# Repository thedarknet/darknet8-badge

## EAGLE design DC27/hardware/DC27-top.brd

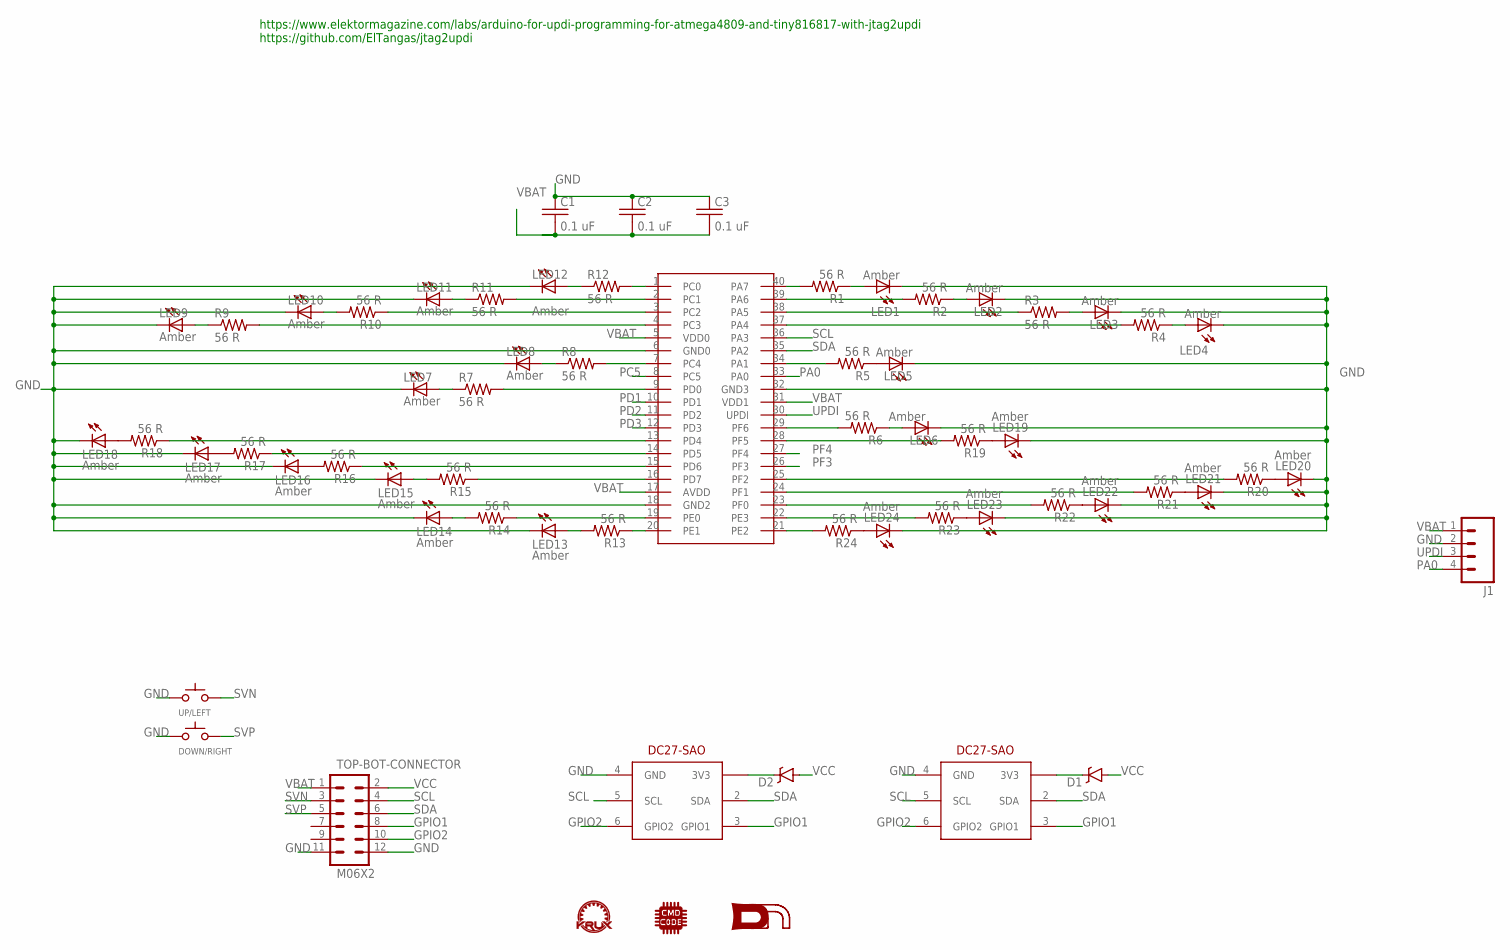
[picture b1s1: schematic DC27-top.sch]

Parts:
C1, C2, C3: 0.1 uF; C1206
D1, D2: DIODE-SCHOTTKYDIOAD-TH; DIOAD1060W80L520D270
DOWN/RIGHT: SWITCH_TACTILETACTILE-2PIN-NARROW; TACTILE-2PIN-NARROW
J1: M04PTH; 1X04
LED1, LED2, LED3, LED4, LED5, LED6, LED7, LED8, LED9, LED10, LED11, LED12, LED13, LED14, LED15, LED16, LED17, LED18, LED19, LED20, LED21, LED22, LED23, LED24: Amber; GULLWING_LED
R1, R2, R3, R4, R5, R6, R7, R8, R9, R10, R11, R12, R13, R14, R15, R16, R17, R18, R19, R20, R21, R22, R23, R24: 56 R; 1206
TOP-BOT-CONNECTOR: M06X2; 2X6
U$1: KRUX_LOGO
U$2: CMD_C0DE_LOGO
U$3, U$4: DC-27-SAO; 3X2
U$5: DN_LOGODC26; DN_LOGO_DC26
U$6: ATMEGA4809-PFATMEL4809-PF; DIP1587W58P254L5175H635Q40B
UP/LEFT: SWITCH_TACTILETACTILE-2PIN-NARROW; TACTILE-2PIN-NARROW

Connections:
GND: C1.1, C2.1, C3.1, DOWN/RIGHT.P$2 (C), J1.2, LED1.C, LED2.C, LED3.C, LED4.C, LED5.C, LED6.C, LED7.C, LED8.C, LED9.C, LED10.C, LED11.C, LED12.C, LED13.C, LED14.C, LED15.C, LED16.C, LED17.C, LED18.C, LED19.C, LED20.C, LED21.C, LED22.C, LED23.C, LED24.C, TOP-BOT-CONNECTOR.11, TOP-BOT-CONNECTOR.12, U$3.4 (GND), U$4.4 (GND), U$6.6 (GND0), U$6.18 (GND2), U$6.32 (GND3), UP/LEFT.P$2 (C)
GPIO1: TOP-BOT-CONNECTOR.8, U$3.3 (GPIO1), U$4.3 (GPIO1)
GPIO2: TOP-BOT-CONNECTOR.10, U$3.6 (GPIO2), U$4.6 (GPIO2)
unnamed: R9.2, U$6.4 (PC3)
unnamed: LED9.A, R9.1
unnamed: R8.2, U$6.7 (PC4)
unnamed: R7.2, U$6.9 (PD0)
unnamed: R1.2, U$6.40 (PA7)
unnamed: R2.2, U$6.39 (PA6)
unnamed: R3.1, U$6.38 (PA5)
unnamed: LED8.A, R8.1
unnamed: LED7.A, R7.1
unnamed: R10.1, U$6.3 (PC2)
unnamed: R11.2, U$6.2 (PC1)
unnamed: R12.2, U$6.1 (PC0)
unnamed: R4.2, U$6.37 (PA4)
unnamed: LED5.A, R5.1
unnamed: R5.2, U$6.34 (PA1)
unnamed: R13.1, U$6.20 (PE1)
unnamed: LED13.A, R13.2
unnamed: R14.1, U$6.19 (PE0)
unnamed: LED14.A, R14.2
unnamed: R15.1, U$6.16 (PD7)
unnamed: LED15.A, R15.2
unnamed: LED17.A, R17.2
unnamed: LED16.A, R16.2
unnamed: R18.1, U$6.13 (PD4)
unnamed: D2.C, U$3.1 (3V3)
unnamed: D1.C, U$4.1 (3V3)
unnamed: R6.2, U$6.29 (PF6)
unnamed: LED6.A, R6.1
unnamed: LED4.A, R4.1
unnamed: LED18.A, R18.2
unnamed: LED1.A, R1.1
unnamed: LED2.A, R2.1
unnamed: R17.1, U$6.14 (PD5)
unnamed: R16.1, U$6.15 (PD6)
unnamed: LED24.A, R24.1
unnamed: LED10.A, R10.2
unnamed: LED11.A, R11.1
unnamed: LED12.A, R12.1
unnamed: LED23.A, R23.1
unnamed: LED22.A, R22.1
unnamed: LED19.A, R19.1
unnamed: LED21.A, R21.1
unnamed: LED20.A, R20.1
unnamed: R19.2, U$6.28 (PF5)
unnamed: R20.2, U$6.25 (PF2)
unnamed: R21.2, U$6.24 (PF1)
unnamed: R22.2, U$6.23 (PF0)
unnamed: R23.2, U$6.22 (PE3)
unnamed: R24.2, U$6.21 (PE2)
unnamed: LED3.A, R3.2
PA0: J1.4, U$6.33 (PA0)
PC5: U$6.8 (PC5)
PD1: U$6.10 (PD1)
PD2: U$6.11 (PD2)
PD3: U$6.12 (PD3)
PF3: U$6.26 (PF3)
PF4: U$6.27 (PF4)
SCL: TOP-BOT-CONNECTOR.4, U$3.5 (SCL), U$4.5 (SCL), U$6.36 (PA3)
SDA: TOP-BOT-CONNECTOR.6, U$3.2 (SDA), U$4.2 (SDA), U$6.35 (PA2)
SVN: TOP-BOT-CONNECTOR.3, UP/LEFT.P$1 (A)
SVP: DOWN/RIGHT.P$1 (A), TOP-BOT-CONNECTOR.5
UPDI: J1.3, U$6.30 (UPDI)
VBAT: C1.2, C2.2, C3.2, J1.1, TOP-BOT-CONNECTOR.1, U$6.5 (VDD0), U$6.17 (AVDD), U$6.31 (VDD1)
VCC: D1.A, D2.A, TOP-BOT-CONNECTOR.2

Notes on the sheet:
https://www.elektormagazine.com/labs/arduino-for-updi-programming-for-atmega4809-and-tiny816817-with-jtag2updi https://github.com/ElTangas/jtag2updi

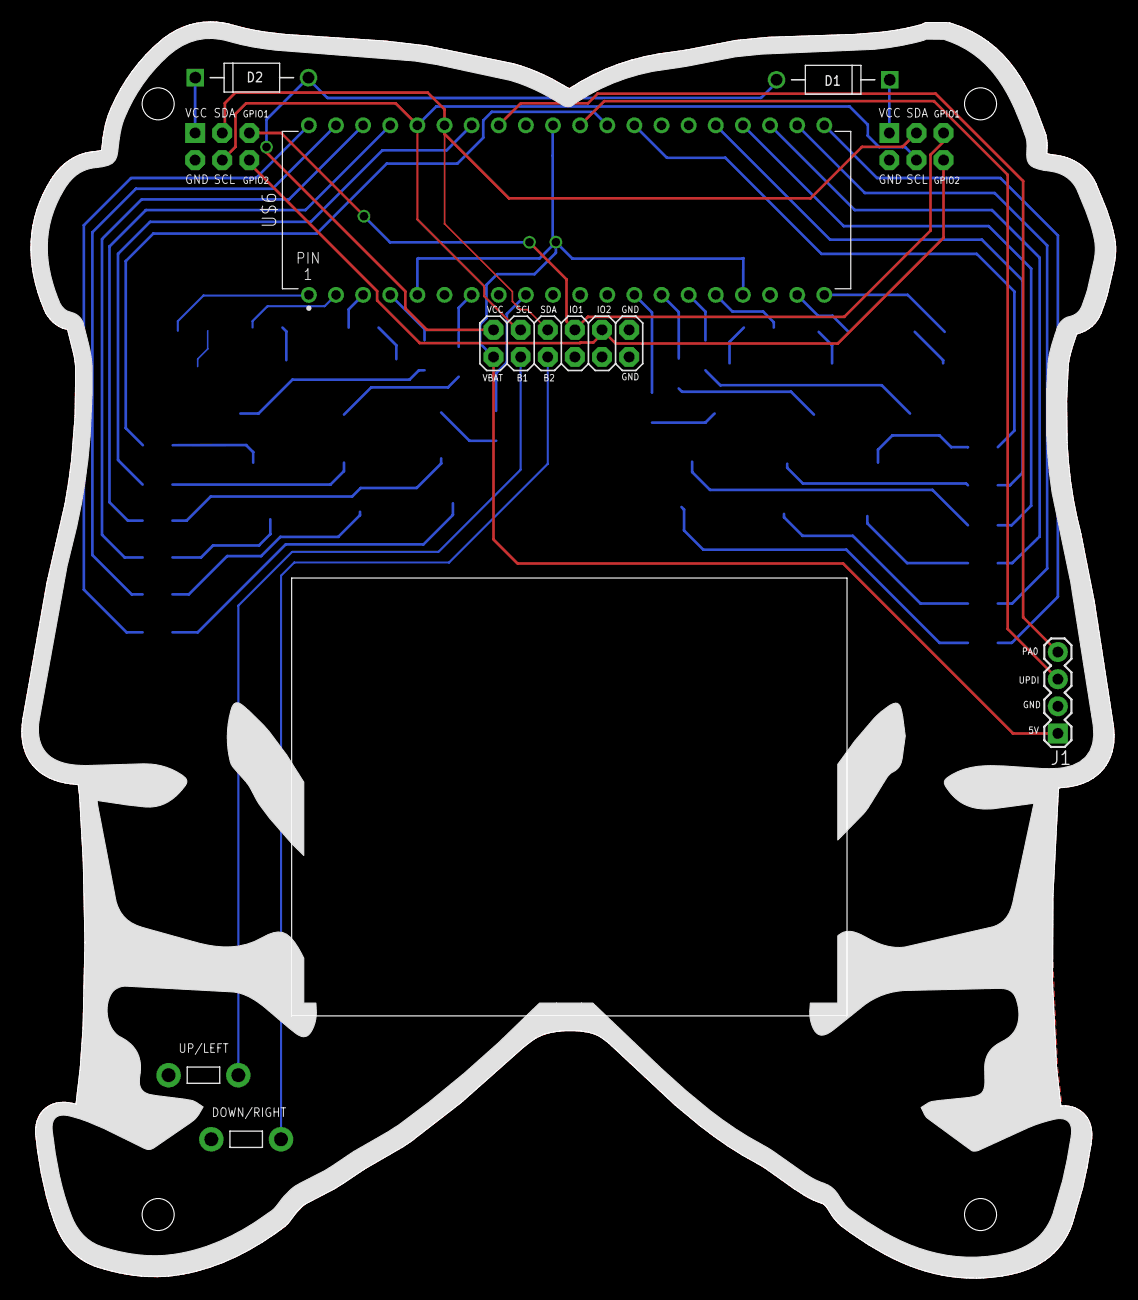
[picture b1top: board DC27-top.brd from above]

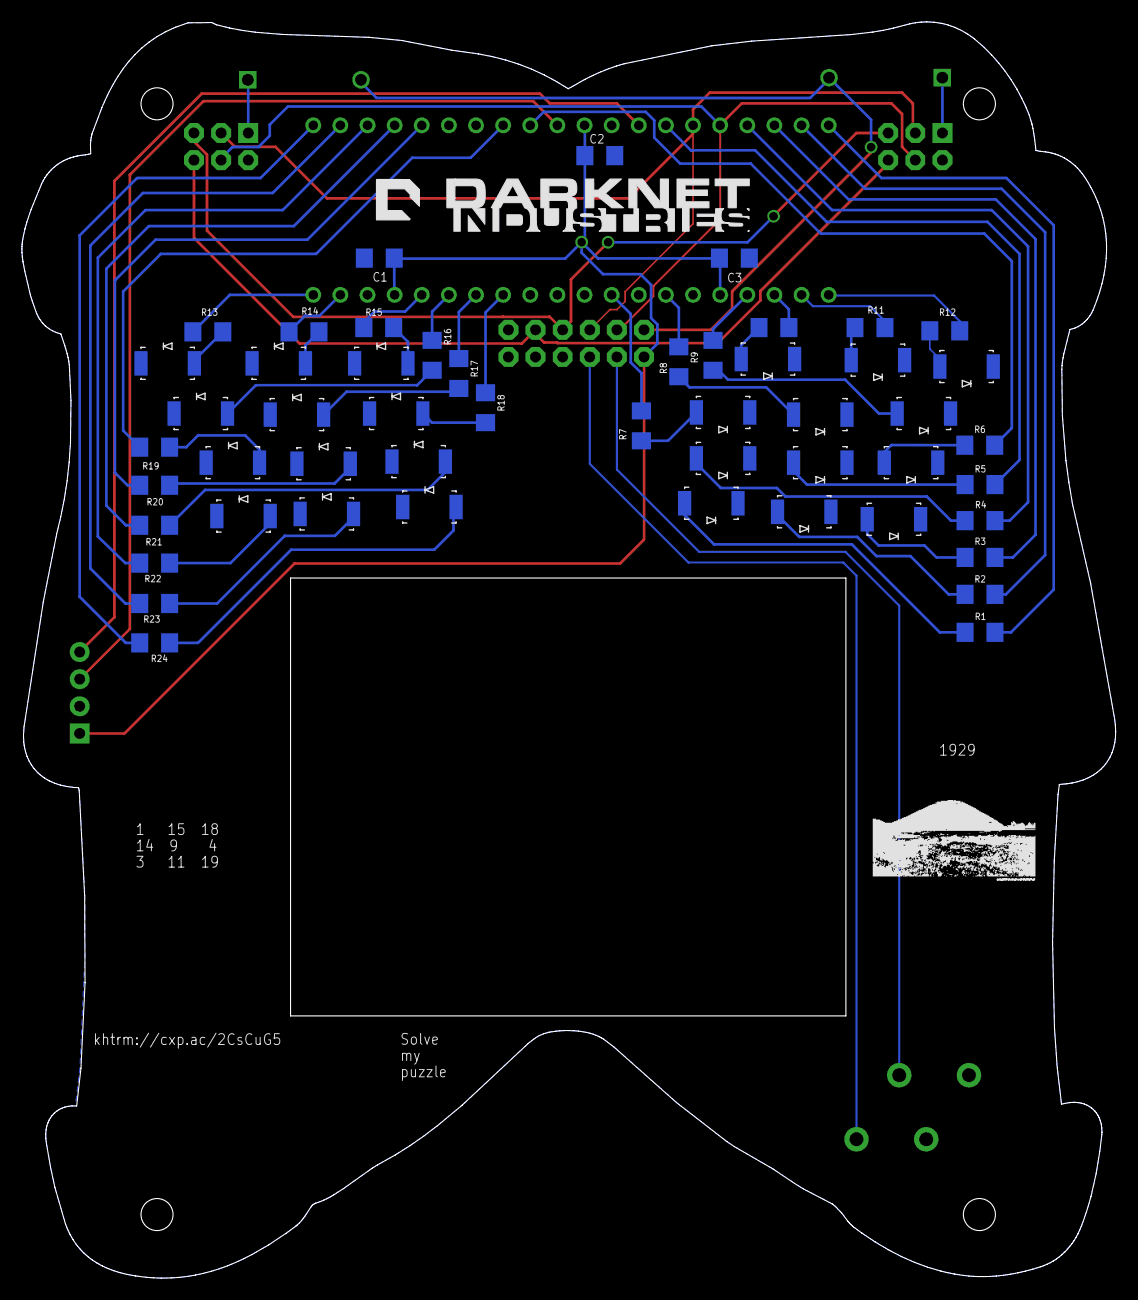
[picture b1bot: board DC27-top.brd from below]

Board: 2 copper layers, 102.4 x 117.6 mm, 63 parts (54 on the bottom side), 61 nets.

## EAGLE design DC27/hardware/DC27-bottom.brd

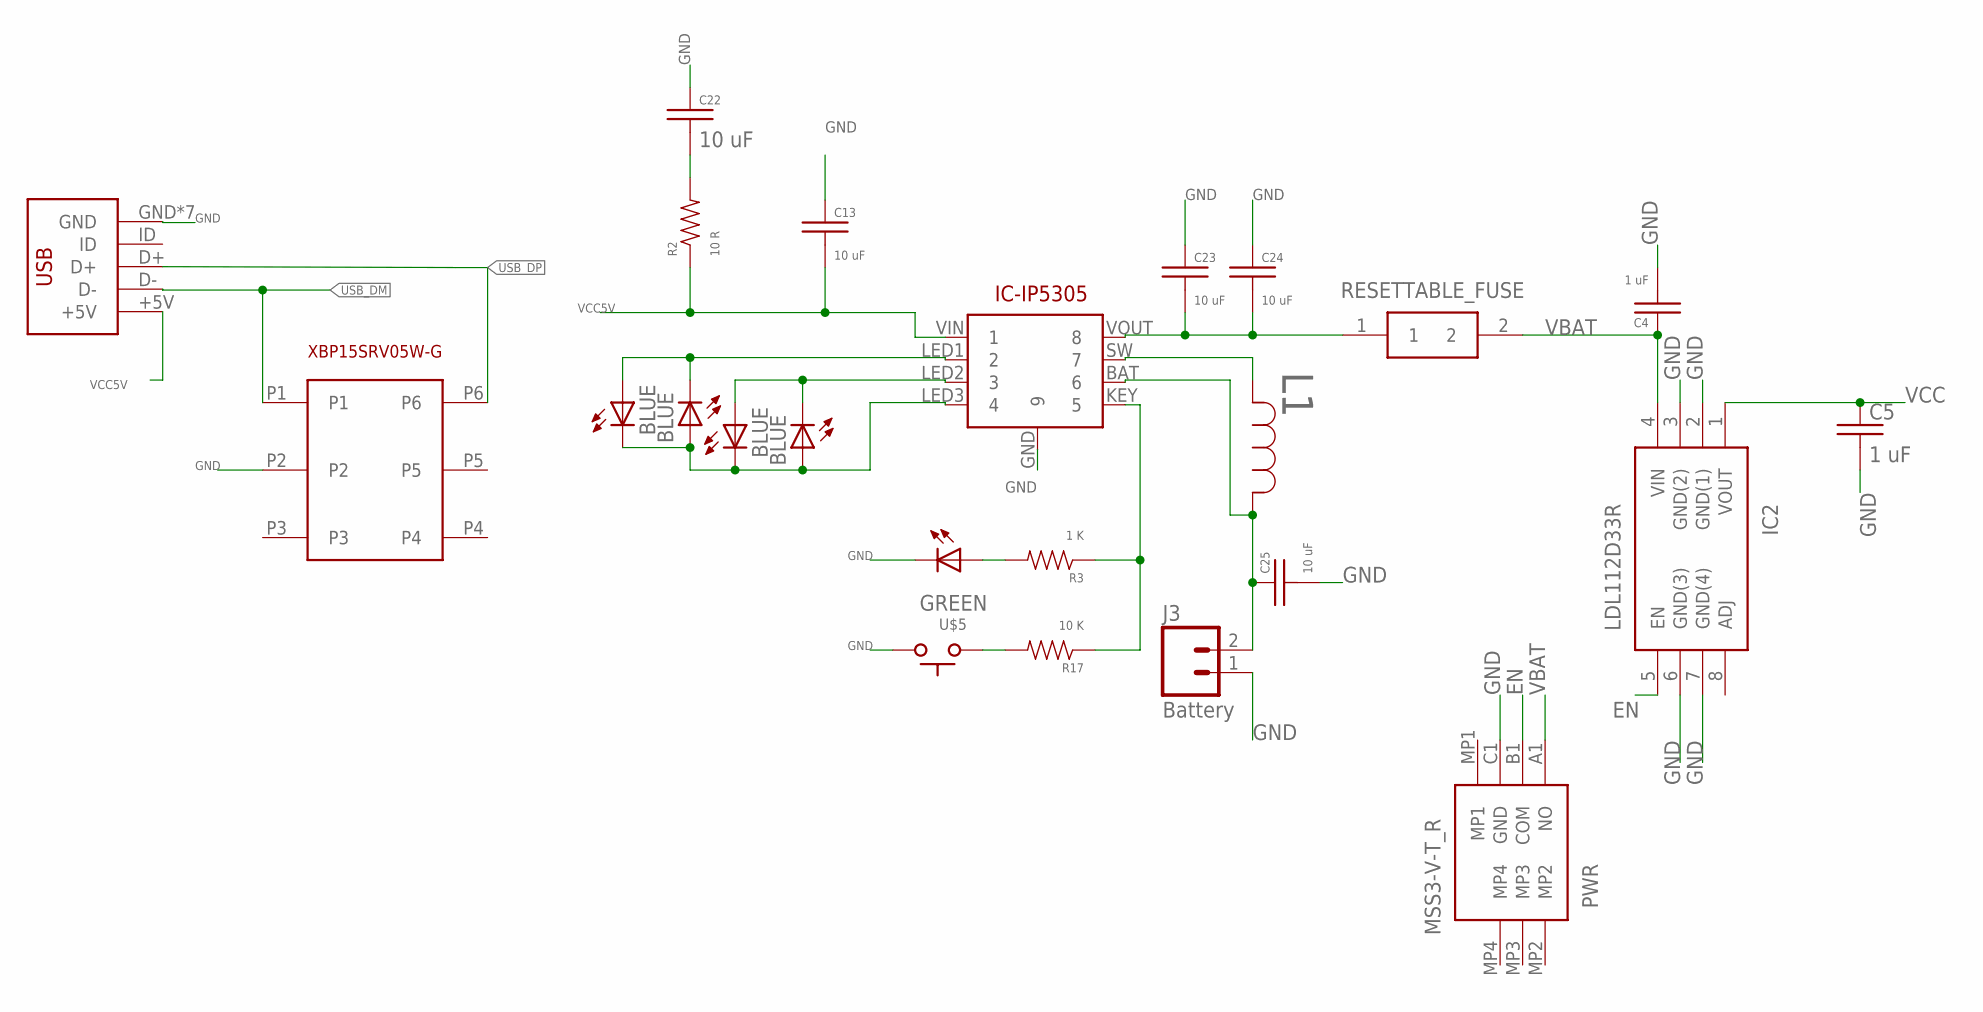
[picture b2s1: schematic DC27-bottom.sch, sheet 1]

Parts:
C4, C5: 1 uF; C0805
C13, C22, C23, C24, C25: 10 uF; C0805
CL1, CL2, CL3, CL4: BLUE; LED-1206
IC2: LDL112D33R; SOIC127P600X175-8N
IC-IP5305: IP5305ESOP8; SOIC127P600X165-8
J3: Battery; JST-2-PTH
KEYLED: GREEN; LED-1206
L1: 2.2uH; IND_TAIYO_NRS4018
PWR: MSS3-V-T_R; MSS3VTR
R2: 10 R; 0805
R3: 1 K; 0805
R17: 10 K; 0805
RESETTABLE_FUSE: 0ZCJ0050FF2G; FUSC3216X55N
U$2: XBP15SRV05W-G; SOT-26P-XBP15SRV05W-G
U$3: DX4R005JJ2DX4R005JJ2; DX4R005JJ2
U$5: SWITCH_TACTILETACTILE-2PIN-NARROW; TACTILE-2PIN-NARROW

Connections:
EN: IC2.5 (EN), PWR.B1 (COM); also elsewhere on the board
GND: C4.2, C5.2, C13.1, C22.1, C23.1, C24.1, C25.2, IC2.2 (GND(1)), IC2.3 (GND(2)), IC2.6 (GND(3)), IC2.7 (GND(4)), IC-IP5305.GND (9), J3.1, KEYLED.C, PWR.C1 (GND), U$2.P2, U$3.GND, U$3.P$6 (GND), U$3.P$7 (GND), U$3.P$8 (GND), U$3.P$9 (GND), U$3.P$10 (GND), U$3.P$11 (GND), U$5.P$1 (A); also elsewhere on the board
unnamed: CL1.A, CL2.C, IC-IP5305.LED1 (2)
unnamed: CL3.A, CL4.C, IC-IP5305.LED2 (3)
unnamed: CL1.C, CL2.A, CL3.C, CL4.A, IC-IP5305.LED3 (4)
unnamed: C22.2, R2.2
unnamed: IC-IP5305.SW (7), L1.2
unnamed: C25.1, IC-IP5305.BAT (6), J3.2, L1.1
unnamed: IC-IP5305.KEY (5), R3.1, R17.1
unnamed: KEYLED.A, R3.2
unnamed: R17.2, U$5.P$2 (C)
unnamed: C23.2, C24.2, IC-IP5305.VOUT (8), RESETTABLE_FUSE.1
USB_DM: U$2.P1, U$3.D-; also elsewhere on the board
USB_DP: U$2.P6, U$3.D+; also elsewhere on the board
VBAT: C4.1, IC2.4 (VIN), PWR.A1 (NO), RESETTABLE_FUSE.2
VCC5V: C13.2, IC-IP5305.VIN (1), R2.1, U$3.+5V; also elsewhere on the board

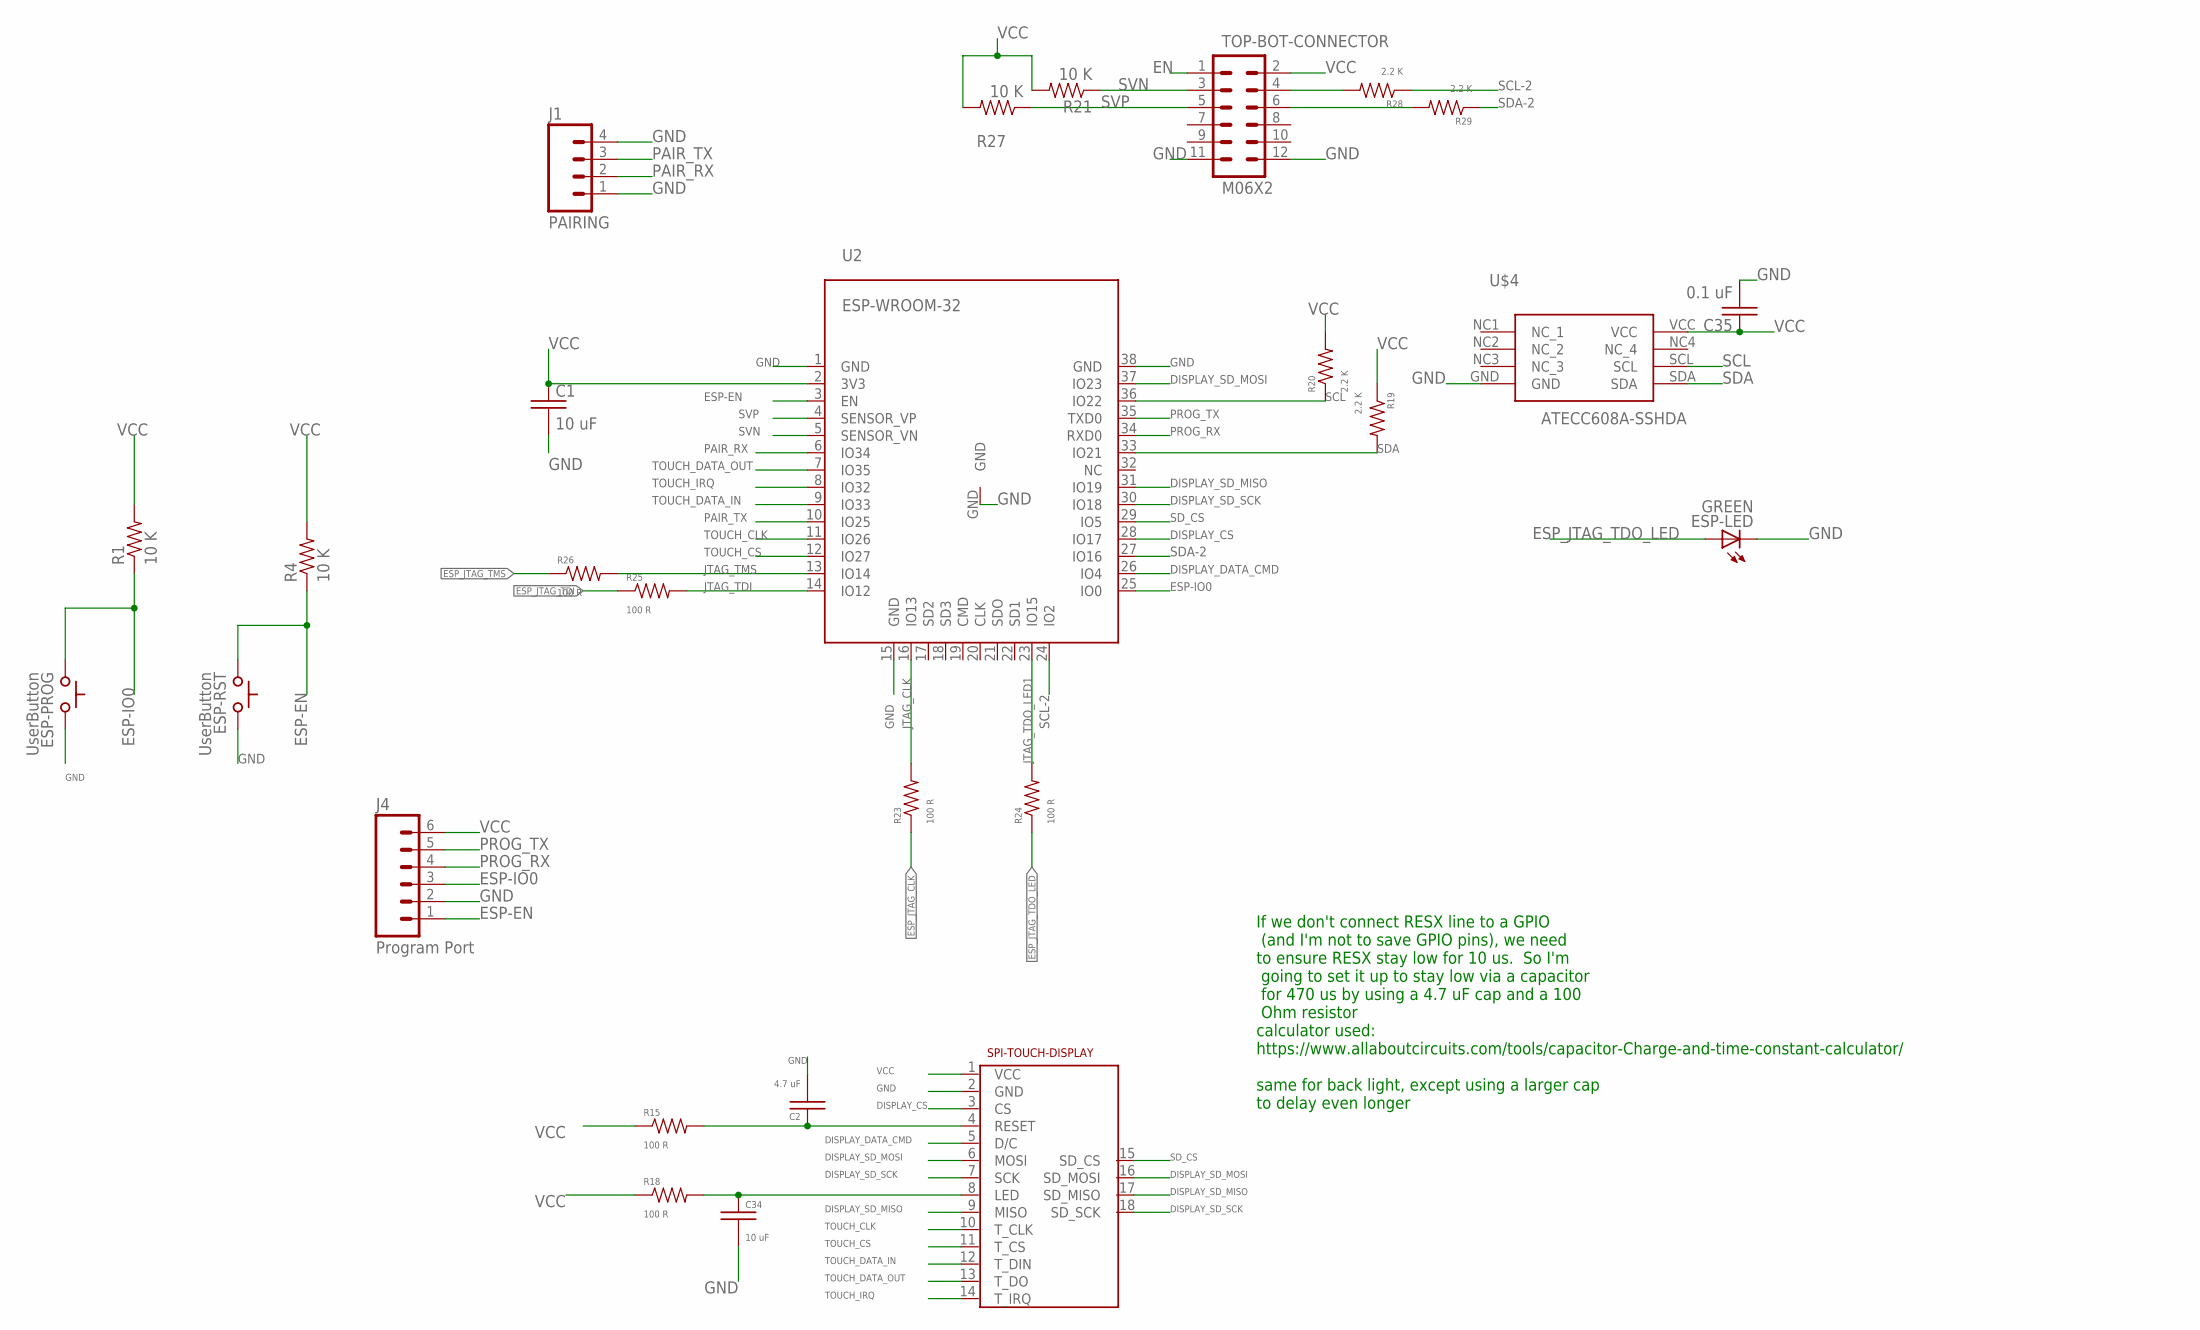
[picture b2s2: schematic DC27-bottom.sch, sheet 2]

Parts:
C1, C34: 10 uF; C0805
C2: 4.7 uF; C0805
C35: 0.1 uF; C0805
ESP-LED: GREEN; LED-1206
ESP-PROG: UserButton; TACTILE-2PIN-NARROW
ESP-RST: UserButton; TACTILE-2PIN-NARROW
J1: PAIRING; 1X04
J4: Program Port; 1X06-SMD-POGO
R1, R4, R21, R27: 10 K; 0805
R15, R18, R23, R24, R25, R26: 100 R; 0805
R19, R20, R28, R29: 2.2 K; 0805
TOP-BOT-CONNECTOR: M06X2; 2X6
U2: ESP-WROOM-32
U$4: ATECC608A-SSHDA; 8-SOIC
U$10: 2.4-SPI-TFT-TOUCH-SSD-MODULE

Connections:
DISPLAY_BACKLIT: C34.1, R18.2, U$10.8 (LED)
DISPLAY_CS: U2.28 (IO17), U$10.3 (CS)
DISPLAY_DATA_CMD: U2.26 (IO4), U$10.5 (D/C)
DISPLAY_RESET: C2.1, R15.2, U$10.4 (RESET)
DISPLAY_SD_MISO: U2.31 (IO19), U$10.9 (MISO), U$10.17 (SD_MISO)
DISPLAY_SD_MOSI: U2.37 (IO23), U$10.6 (MOSI), U$10.16 (SD_MOSI)
DISPLAY_SD_SCK: U2.30 (IO18), U$10.7 (SCK), U$10.18 (SD_SCK)
EN: TOP-BOT-CONNECTOR.1; also elsewhere on the board
ESP-EN: ESP-RST.P$2 (C), J4.1, R4.1, U2.3 (EN)
ESP-IO0: ESP-PROG.P$2 (C), J4.3, R1.1, U2.25 (IO0)
ESP_JTAG_CLK: R23.1; also elsewhere on the board
ESP_JTAG_TDI: R25.1; also elsewhere on the board
ESP_JTAG_TDO_LED: ESP-LED.A, R24.1; also elsewhere on the board
ESP_JTAG_TMS: R26.1; also elsewhere on the board
GND: C1.2, C2.2, C34.2, C35.2, ESP-LED.C, ESP-PROG.P$1 (A), ESP-RST.P$1 (A), J1.1, J1.4, J4.2, TOP-BOT-CONNECTOR.11, TOP-BOT-CONNECTOR.12, U2.1 (GND), U2.15 (GND), U2.38 (GND), U2.GND, U$4.GND, U$10.2 (GND); also elsewhere on the board
JTAG_CLK: R23.2, U2.16 (IO13)
JTAG_TDI: R25.2, U2.14 (IO12)
JTAG_TDO_LED1: R24.2, U2.23 (IO15)
JTAG_TMS: R26.2, U2.13 (IO14)
PAIR_RX: J1.2, U2.6 (IO34)
PAIR_TX: J1.3, U2.10 (IO25)
PROG_RX: J4.4, U2.34 (RXD0); also elsewhere on the board
PROG_TX: J4.5, U2.35 (TXD0); also elsewhere on the board
SCL: R20.1, U2.36 (IO22), U$4.SCL
SDA: R19.2, U2.33 (IO21), U$4.SDA
SD_CS: U2.29 (IO5), U$10.15 (SD_CS)
SVN: R21.1, TOP-BOT-CONNECTOR.3, U2.5 (SENSOR_VN)
SVP: R27.1, TOP-BOT-CONNECTOR.5, U2.4 (SENSOR_VP)
TOUCH_CLK: U2.11 (IO26), U$10.10 (T_CLK)
TOUCH_CS: U2.12 (IO27), U$10.11 (T_CS)
TOUCH_DATA_IN: U2.9 (IO33), U$10.12 (T_DIN)
TOUCH_DATA_OUT: U2.7 (IO35), U$10.13 (T_DO)
TOUCH_IRQ: U2.8 (IO32), U$10.14 (T_IRQ)

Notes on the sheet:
If we don't connect RESX line to a GPIO (and I'm not to save GPIO pins), we need to ensure RESX stay low for 10 us. So I'm going to set it up to stay low via a capacitor for 470 us by using a 4.7 uF cap and a 100 Ohm resistor calculator used: https://www.allaboutcircuits.com/tools/capacitor-Charge-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

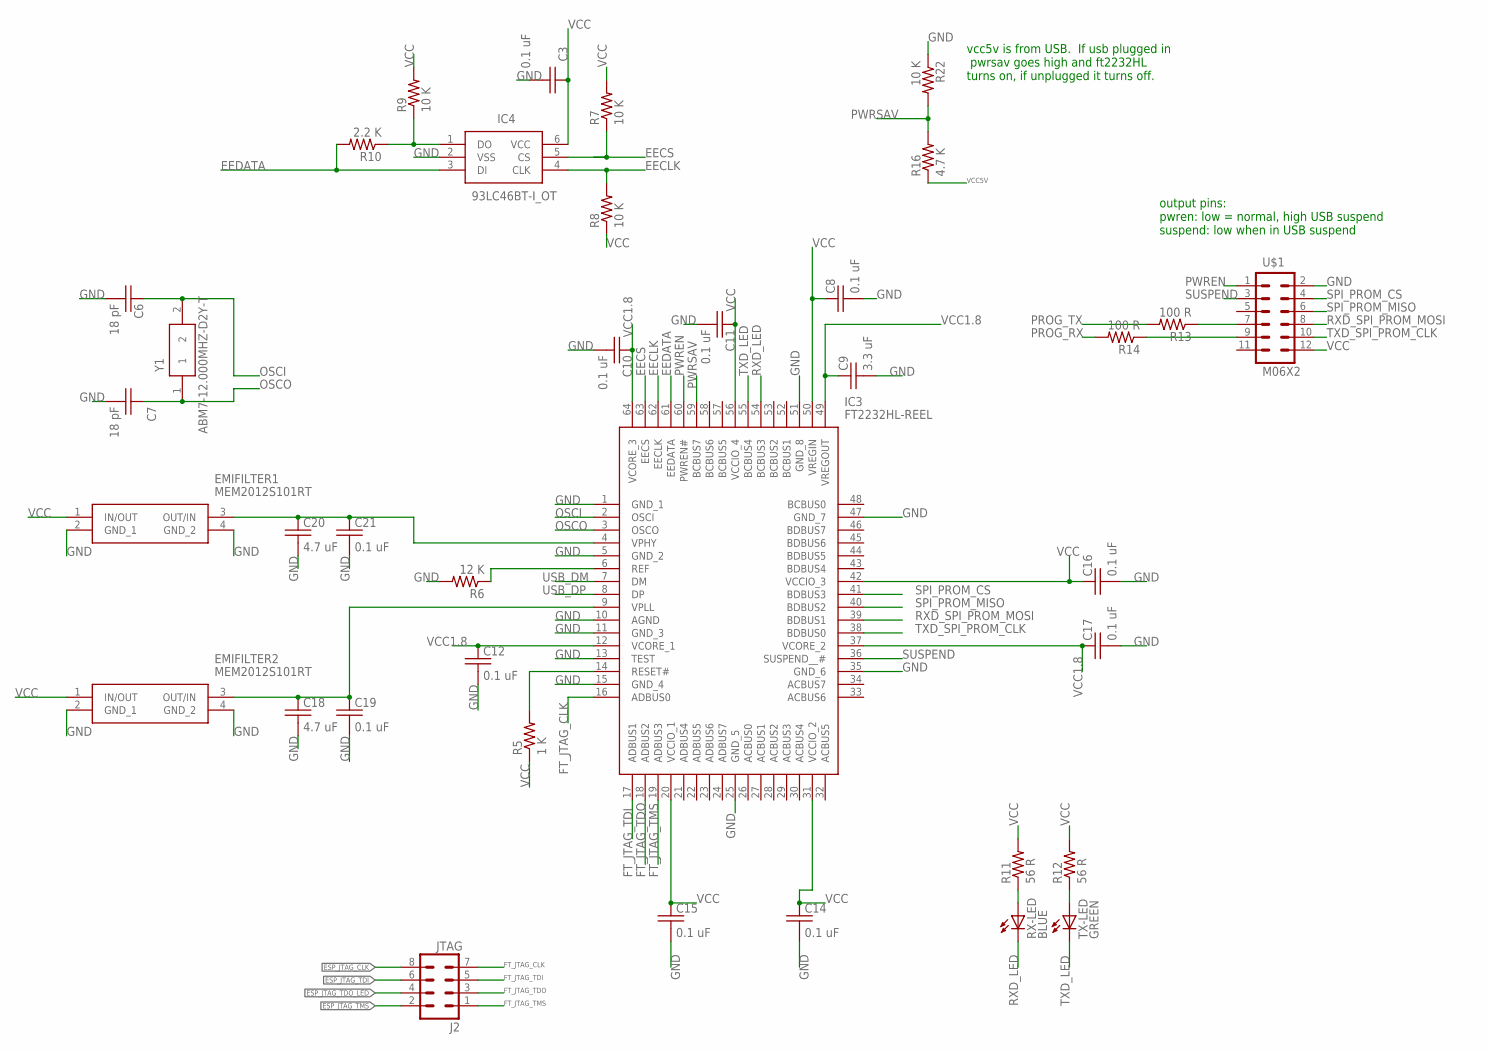
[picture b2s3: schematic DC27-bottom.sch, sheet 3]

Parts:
C3, C8, C10, C11, C12, C14, C15, C16, C17, C19, C21: 0.1 uF; C0805
C6, C7: 18 pF; C0805
C9: 3.3 uF; C0805
C18, C20: 4.7 uF; C0805
EMIFILTER1, EMIFILTER2: MEM2012S101RT
IC3: FT2232HL-REEL; QFP50P1200X1200X160-64N
IC4: 93LC46BT-I_OT; SOT95P270X145-6N
J2: JTAG; 2X4
R5: 1 K; 0805
R6: 12 K; 0805
R7, R8, R9, R22: 10 K; 0805
R10: 2.2 K; 0805
R11, R12: 56 R; 0805
R13, R14: 100 R; 0805
R16: 4.7 K; 0805
RX-LED: BLUE; LED-1206
TX-LED: GREEN; LED-1206
U$1: M06X2; 2X6
Y1: ABM7-12.000MHZ-D2Y-T; ABM7

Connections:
EECLK: IC3.62 (EECLK), IC4.4 (CLK), R8.2
EECS: IC3.63 (EECS), IC4.5 (CS), R7.1
EEDATA: IC3.61 (EEDATA), IC4.3 (DI), R10.2
ESP_JTAG_CLK: J2.8; also elsewhere on the board
ESP_JTAG_TDI: J2.6; also elsewhere on the board
ESP_JTAG_TDO_LED: J2.4; also elsewhere on the board
ESP_JTAG_TMS: J2.2; also elsewhere on the board
FT_JTAG_CLK: IC3.16 (ADBUS0), J2.7
FT_JTAG_TDI: IC3.17 (ADBUS1), J2.5
FT_JTAG_TDO: IC3.18 (ADBUS2), J2.3
FT_JTAG_TMS: IC3.19 (ADBUS3), J2.1
GND: C3.2, C6.2, C7.2, C8.2, C9.2, C10.2, C11.2, C12.2, C14.2, C15.2, C16.2, C17.2, C18.2, C19.2, C20.2, C21.2, EMIFILTER1.2 (GND_1), EMIFILTER1.4 (GND_2), EMIFILTER2.2 (GND_1), EMIFILTER2.4 (GND_2), IC3.1 (GND_1), IC3.5 (GND_2), IC3.10 (AGND), IC3.11 (GND_3), IC3.13 (TEST), IC3.15 (GND_4), IC3.25 (GND_5), IC3.35 (GND_6), IC3.47 (GND_7), IC3.51 (GND_8), IC4.2 (VSS), R6.2, R22.1, U$1.2; also elsewhere on the board
unnamed: IC3.14 (RESET#), R5.2
unnamed: IC3.6 (REF), R6.1
unnamed: IC4.1 (DO), R9.1, R10.1
unnamed: R11.1, RX-LED.A
unnamed: R12.1, TX-LED.A
unnamed: C18.1, C19.1, EMIFILTER2.3 (OUT/IN), IC3.9 (VPLL)
unnamed: C20.1, C21.1, EMIFILTER1.3 (OUT/IN), IC3.4 (VPHY)
unnamed: R14.1, U$1.9
unnamed: R13.1, U$1.7
OSCI: C6.1, IC3.2 (OSCI), Y1.2
OSCO: C7.1, IC3.3 (OSCO), Y1.1
PROG_RX: R14.2; also elsewhere on the board
PROG_TX: R13.2; also elsewhere on the board
PWREN: IC3.60 (PWREN#), U$1.1
PWRSAV: IC3.59 (BCBUS7), R16.2, R22.2
RXD_LED: IC3.54 (BCBUS3), RX-LED.C
RXD_SPI_PROM_MOSI: IC3.39 (BDBUS1), U$1.8
SPI_PROM_CS: IC3.41 (BDBUS3), U$1.4
SPI_PROM_MISO: IC3.40 (BDBUS2), U$1.6
SUSPEND: IC3.36 (SUSPEND__#), U$1.3
TXD_LED: IC3.55 (BCBUS4), TX-LED.C
TXD_SPI_PROM_CLK: IC3.38 (BDBUS0), U$1.10
USB_DM: IC3.7 (DM); also elsewhere on the board
USB_DP: IC3.8 (DP); also elsewhere on the board
VCC1.8: C9.1, C10.1, C12.1, C17.1, IC3.12 (VCORE_1), IC3.37 (VCORE_2), IC3.49 (VREGOUT), IC3.64 (VCORE_3)
VCC5V: R16.1; also elsewhere on the board

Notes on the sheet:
output pins: pwren: low = normal, high USB suspend suspend: low when in USB suspend
vcc5v is from USB. If usb plugged in pwrsav goes high and ft2232HL turns on, if unplugged it turns off.

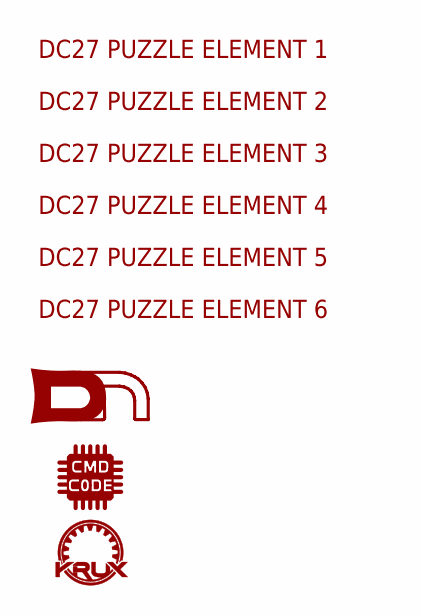
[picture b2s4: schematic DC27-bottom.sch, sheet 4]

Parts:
U$6: DC27_PUZZLE_ELEMENT_1
U$7: KRUX_LOGO
U$8: CMD_C0DE_LOGO
U$9: DN_LOGODC26; DN_LOGO_DC26
U$11: DC27_PUZZLE_ELEMENT_2
U$12: DC27_PUZZLE_ELEMENT_3
U$13: DC27_PUZZLE_ELEMENT_4
U$14: DC27_PUZZLE_ELEMENT_5
U$15: DC27_PUZZLE_ELEMENT_6

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
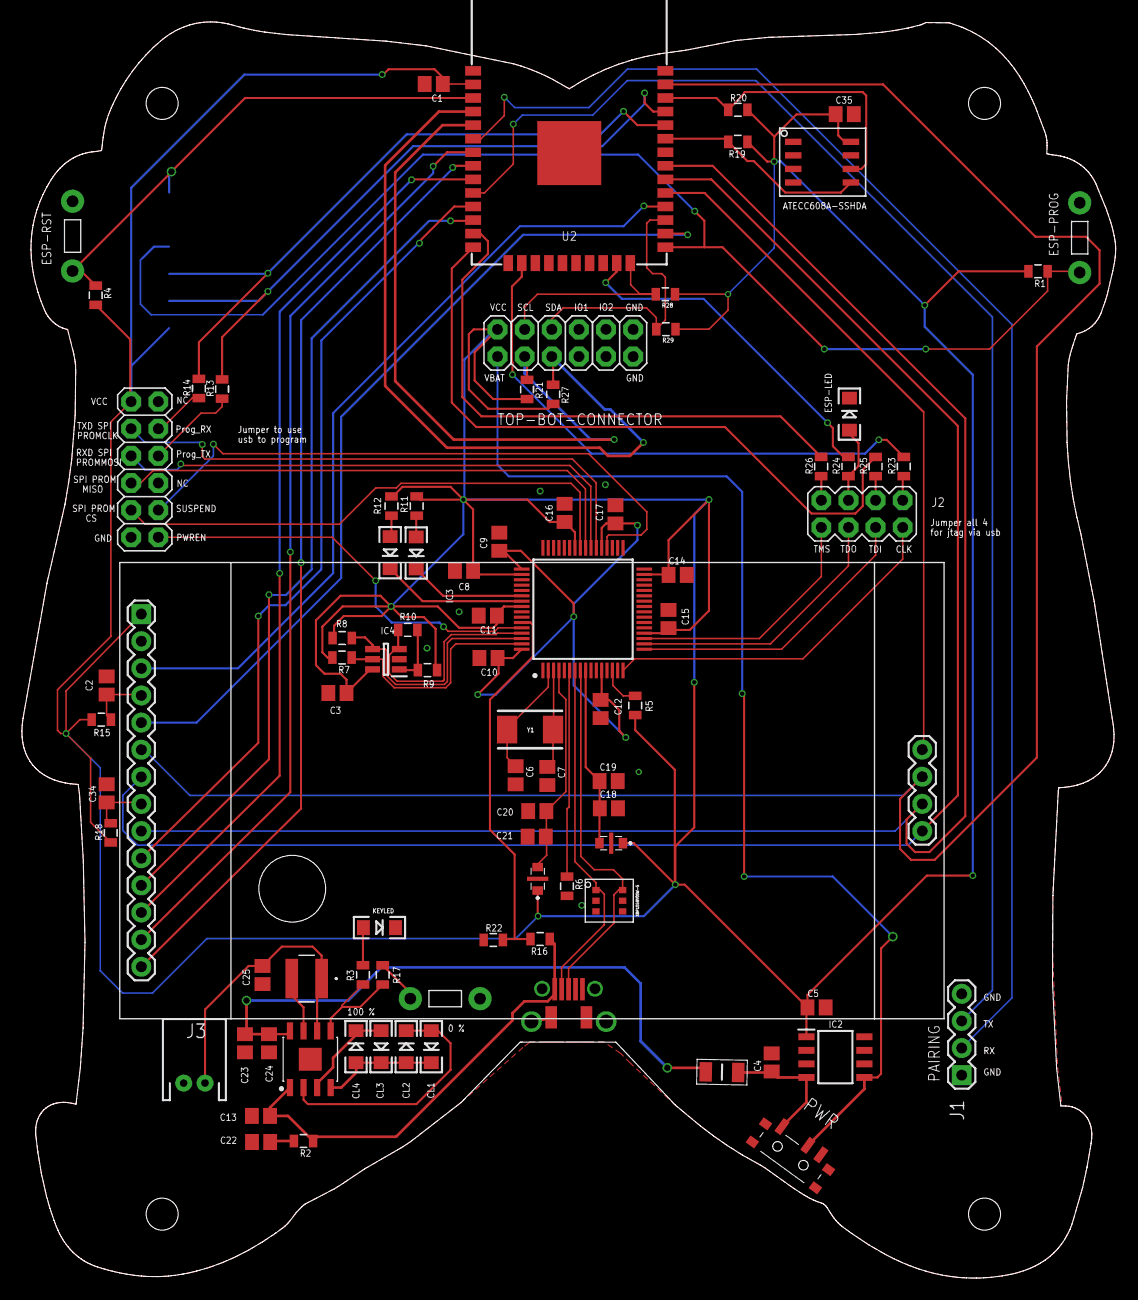
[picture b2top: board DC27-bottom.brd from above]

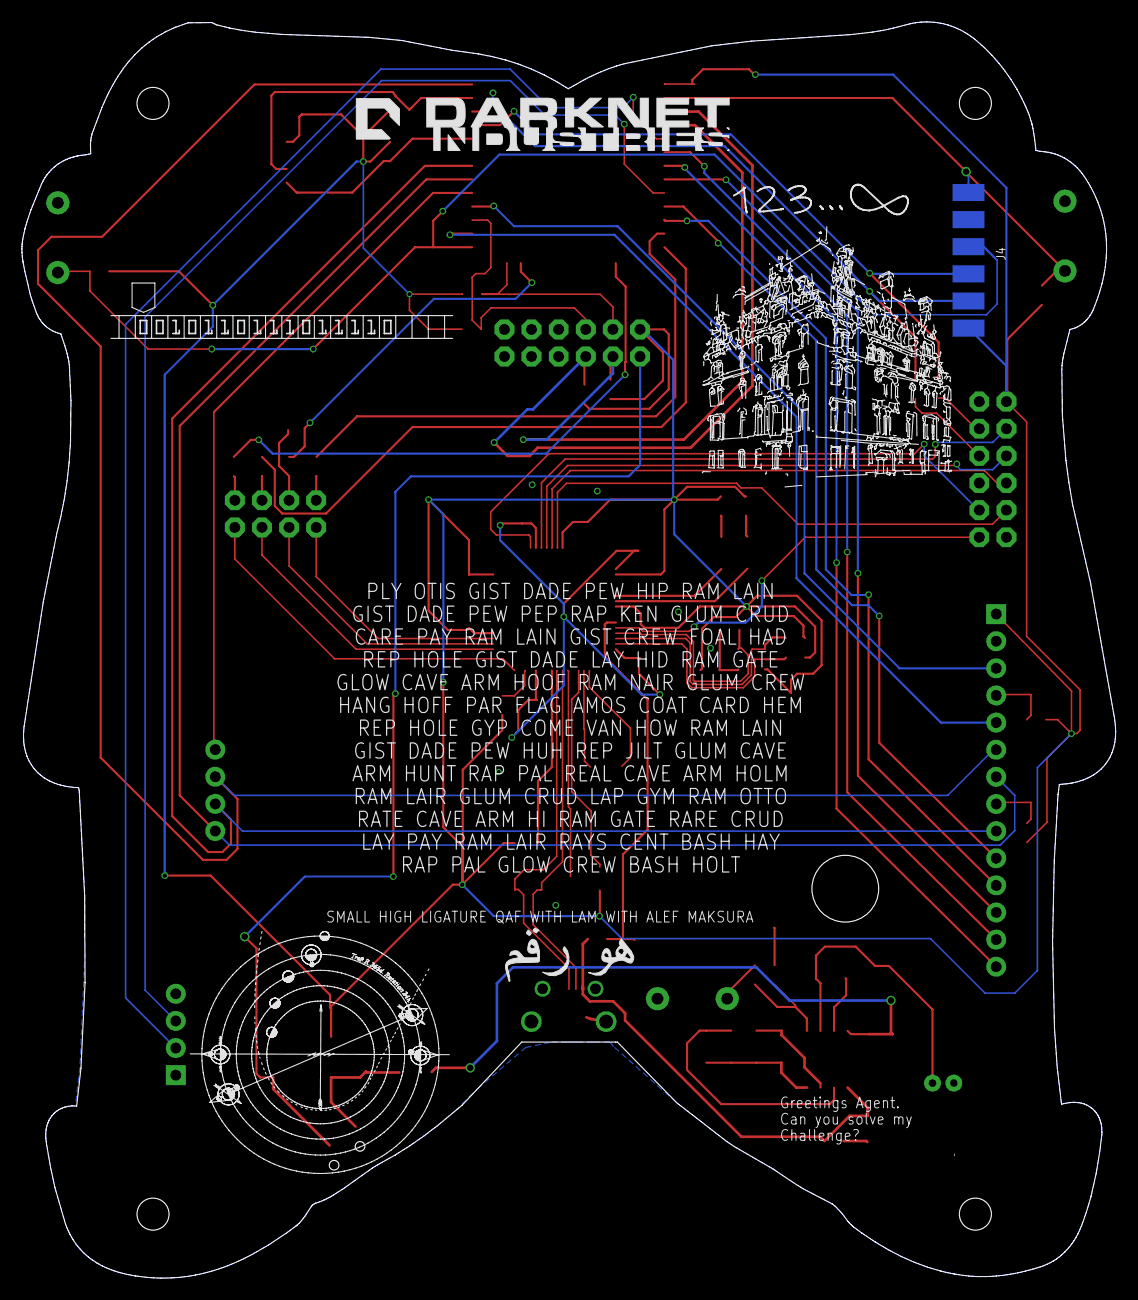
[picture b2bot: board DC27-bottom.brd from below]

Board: 2 copper layers, 102.4 x 117.6 mm, 97 parts (10 on the bottom side), 78 nets.
